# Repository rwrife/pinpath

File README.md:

# PinPath

> USB-powered RP2040 cable and wiring-harness tester for makers to map low-voltage pin continuity, catch opens, shorts, and crossovers, and save local test reports without cloud accounts.

## Overview

PinPath is planned as safe, repairable, open hardware for checking **disconnected, de-energized** passive cables and small wiring harnesses at a desk or workbench. Two configurable 16-position test banks connect through replaceable adapter boards or labeled flying leads. Firmware scans the conductors, reports the observed end-to-end map, and compares it with a user-selected expected map. A local desktop companion creates cable profiles and exports results.

This repository contains the frozen MVP requirements/architecture, a manufacturer-backed **rev-A candidate component selection**, the editable rev-A carrier schematic and routed carrier PCB candidate with source-of-truth BOM and clean native ERC/DRC evidence, RP2040 firmware with host-test scenario coverage, the Tauri 2 companion app with deterministic mock-protocol tests, and assembly/bring-up documentation. It still does not contain a fabricated unit or any bench-test evidence; `hardware/selection/limits-rev-a.json` deliberately keeps scanning unauthorized until physical characterization, and no release tag exists until that evidence does.

## Motivation

Continuity mode on a multimeter works for one conductor at a time, but repetitive multi-pin checks are slow and easy to record incorrectly. Commercial harness testers can be excessive for hobby and repair work. PinPath aims to make common passive-cable checks repeatable while keeping the limits obvious: it is not a live-circuit probe, cable certifier, insulation tester, or safety instrument.

## Target users

- Makers assembling Dupont, JST-style, ribbon, and custom low-voltage harnesses
- Repair hobbyists checking intermittent or miswired passive cables
- Small workshops repeating the same fixture check in low volume
- Electronics learners who want a visible pin-to-pin map

## Concrete use cases

1. Connect both ends of an unpowered 10-conductor ribbon harness through adapters, select its saved profile, and identify one crossed pair.
2. Wiggle a repaired USB-data-only breakout harness during a timed scan and flag intermittent continuity for investigation; do **not** connect a live USB source.
3. Map an undocumented passive cable, label its observed connections, and export JSON/CSV for a project record.
4. Run a fixture self-test using a known loopback adapter before testing a batch.

## Intended workflow

1. Disconnect the cable or harness from every power source and device.
2. Inspect it and connect each end to the appropriate passive adapter or labeled flying leads.
3. Choose **map unknown cable** or an expected cable profile in the desktop app.
4. Start a bounded scan from the app or device button.
5. Review opens, shorts, crossovers, and intermittent observations; save or export the report.
6. Disconnect the item under test before changing adapters.

## MVP features

- Up to 16 conductors per side through two protected test banks
- Deterministic continuity map with open, short, and crossover classification
- Fixture self-test and explicit connected-voltage precheck design requirement
- Physical start/cancel button and non-color-only status indication
- USB CDC protocol; useful offline without Wi-Fi or an account
- Local profile/history storage with versioned JSON backup and CSV report export
- Replaceable adapter interface, starting with pin headers and labeled flying leads

## Non-goals

- Testing energized cables, mains wiring, PoE, batteries or battery packs, powered USB through a test bank, vehicles, medical or life-safety wiring, or unknown live circuits
- USB/Ethernet signal-integrity, bandwidth, impedance, insulation, hipot, precision-resistance, cable certification, or other certification measurements
- Four-wire milliohm measurement or calibrated resistance metrology
- Automatic connector identification
- Cloud dashboards, remote unattended operation, or production-line certification claims

## Safety and electrical limits

PinPath is planned for USB SELV power and de-energized passive assemblies only. The design must detect unexpected external voltage before enabling continuity scans, limit fault current, tolerate routine static handling, and fail visibly. These protections reduce risk but do not make live testing acceptable. Never connect mains, PoE, battery packs, powered USB hosts, vehicles, medical equipment, or safety-critical wiring. Final voltage/current limits will be set only after component datasheet review and measured bring-up.

## Privacy, permissions, and data storage

The desktop app will work locally with no account, telemetry, advertising, or cloud dependency. It requests USB-device access only when the user connects to PinPath and filesystem access only for explicit import/export. Profiles and reports live in an app-local SQLite database. Versioned JSON backup/restore and CSV report export keep the data user-owned. Export can omit free-text project notes.

## Accessibility expectations

All status must be conveyed with text/icon shape in addition to color. The app must support keyboard-only operation, screen readers, scalable text, strong focus indicators, reduced motion, and high-contrast themes. Connector positions and adapter documentation must use durable numbers, not color alone.

## Planned repository layout

```text
hardware/pinpath.kicad_pro    # editable rev-A carrier project
hardware/pinpath.kicad_sch    # editable carrier schematic and BOM source of truth
hardware/pinpath.kicad_pcb    # routed rev-A carrier candidate (see hardware/PCB-layout-evidence.md)
hardware/adapters/            # known-loopback electrical definition; PCB adapters planned
hardware/selection/           # rev-A candidate parts, evidence, calculations, and unvalidated limits
hardware/reports/             # ERC/DRC evidence and host-sim integration matrix
hardware/fab-out/             # gerber/drill/CPL candidates, fab inspection, board renders
firmware/                     # RP2040 safe-state firmware, host tests, scenario matrix, HIL fixture
app/                          # Tauri 2 desktop companion (Rust + TypeScript)
bom/bom.csv                   # schematic-derived tracked BOM
bom/non-schematic-items.csv   # cables, contacts, tools, and mechanical items
docs/                         # architecture, protocol, risk, verification matrix, assembly/bring-up docs
release/                      # release-readiness checklist and checksum generator
```

Final BOM data belongs in **KiCad schematic symbol properties** (including Manufacturer and MPN) and is exported to tracked `bom/bom.csv`. The preliminary CSV remains planning history; neither file is an order or a claim of current stock/price validation.

## Current status and milestones

- **Now:** frozen MVP requirements/architecture, rev-A candidate component selection, editable carrier schematic and routed carrier PCB candidate (0-error DRC, documented residuals), clean native ERC, schematic-derived BOM, RP2040 safe-state firmware with host tests and a 13-scenario integration matrix (host simulation), desktop companion with lint/tests/a11y/build/unsigned-package CI, assembly/bring-up/characterization documentation, and a release-readiness checklist (`release/RELEASE-READINESS.md`). Physical fabrication, assembly, and bench validation remain pending; scanning stays unauthorized until the limits record is validated on real hardware.
- **M1:** requirements, risk analysis, and adapter/test architecture
- **M2:** datasheet-backed component selection, editable KiCad schematic, and clean/documented ERC
- **M3:** PCB, DRC, firmware, protocol, and simulated fixture tests
- **M4:** desktop app, integration bring-up, assembly documentation, and measured limits
- **M5:** inspected fabrication outputs and reproducible release archive

## Development quickstart

The current repeatable static checks are:

```bash
python3 tools/verify_requirements.py
python3 hardware/selection/calculate_frontend.py --output hardware/selection/front-end-analysis.json
python3 -m unittest discover -s hardware/selection -p 'test_*.py' -v
python3 tools/verify_component_selection.py
python3 tools/verify_schematic.py
kicad-cli sch erc hardware/pinpath.kicad_sch --severity-all --exit-code-violations -o hardware/reports/pinpath-erc.rpt
```

After implementation skeletons land, expected commands are:

```bash
# Firmware (planned)
cmake -S firmware -B firmware/build
cmake --build firmware/build
ctest --test-dir firmware/build

# Desktop app (current baseline)
cd app
npm ci
npm run lint
npm run test:ci
npm run a11y
npm run build
npm run tauri:build
```

The firmware commands remain architectural targets. The app commands are now wired in CI and pass locally on this branch. See [PLAN.md](PLAN.md), [system requirements](hardware/requirements.md), [architecture](docs/architecture.md), [risk analysis](docs/risk-analysis.md), [verification matrix](docs/verification-matrix.md), [app/README.md](app/README.md), and [docs/usb-permissions.md](docs/usb-permissions.md) for status and limitations.

## Licensing

Software and documentation are MIT licensed (`LICENSE`); editable KiCad
hardware sources are distributed under the same MIT grant for the rev-A
candidate. Third-party code and documentation references are attributed in
[THIRD_PARTY_NOTICES.md](THIRD_PARTY_NOTICES.md). Manufacturer datasheets cited
in `hardware/selection/evidence-sources.json` remain the property of their
respective manufacturers.

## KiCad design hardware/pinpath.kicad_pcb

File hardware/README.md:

# Hardware plan

## System block description

```text
USB 5 V SELV
    |
[power/protection] -> [RP2040 module + USB CDC]
                            |
                  [protected scan front end]
                     /                \
             [16-pin Bank A]      [16-pin Bank B]
                     |                  |
              passive adapter     passive adapter
                       \              /
                    de-energized cable
```

The rev-A schematic uses Raspberry Pi Pico `SC0915`, eight TI `TMUX1108PWR` muxes for independent stimulus/sense paths, 10 kΩ endpoint current limiting, low-leakage rail clamps, four-channel ESD arrays, and a two-phase 0/1.8 V precheck bias. The editable project is now in `pinpath.kicad_pro` / `pinpath.kicad_sch`; exact references, packages, manufacturer properties, GPIO allocation, and pinout evidence are in [the component-selection handoff](selection/component-selection.md) and [schematic pinout evidence](schematic-pinout-evidence.md). Native KiCad 9 ERC is clean, but this remains static EDA evidence only: `selection/limits-rev-a.json` is still `validated: false`, so no scan is authorized before layout review and bench characterization. Normative behavior and evidence gates remain in [requirements](requirements.md), [architecture](../docs/architecture.md), [risk analysis](../docs/risk-analysis.md), and the [verification matrix](../docs/verification-matrix.md).

## Interfaces

- USB CDC for power, configuration, and reports
- Two keyed 16-position low-voltage test-bank connectors
- Replaceable passive adapters; first targets are numbered headers and labeled flying leads
- SWD or vendor-supported debug connection and a documented recovery path
- Physical start/cancel control and text/shape-capable or coded status indication

## Power plan

USB 5 V SELV enters only through the Pico micro-USB connector; its on-module supply generates 3V3 for the candidate front end. The two-phase precheck requires all 32 endpoints to track both a low bias and the measured 1.8 V reference while every stimulus enable is low. Provisional thresholds and calculated fault currents are recorded in `selection/limits-rev-a.json`, but are explicitly unvalidated and cannot authorize firmware scanning. The design must not source meaningful operating power into the item under test.

## Enclosure and assembly concept

A small screw-fastened or snap-fit printed enclosure will expose the two adapter sockets, USB, button, and status window. The PCB will use hand-assembly-friendly parts where practical, mounting holes, clear pin numbering, probeable test points, and replaceable adapters so connector wear does not require replacing the main board.

## Safety limits

Use only with fully disconnected, de-energized passive cables and harnesses. Never attach mains, PoE, powered USB through a test bank, a battery or battery pack, vehicles, medical or life-safety wiring, or any energized circuit. PinPath makes no cable certification claim and is not a hipot tester, insulation tester, precision ohmmeter, or protective instrument. Protection circuitry cannot make prohibited live testing safe.

## Editable KiCad deliverables

Current schematic-stage sources and evidence are:

- `hardware/pinpath.kicad_pro`
- `hardware/pinpath.kicad_sch`
- `hardware/pinpath.kicad_pcb` (rev-A carrier layout candidate; see [PCB layout evidence](PCB-layout-evidence.md) for DRC status, residuals, and fab-candidate posture)
- `hardware/pinpath.kicad_sym`
- `hardware/pinpath.pretty/RaspberryPi_Pico_SMD_HandSolder.kicad_mod`
- `hardware/TestPoint.pretty/` (project-local micro test points)
- `hardware/schematic-pinout-evidence.md`
- `hardware/PCB-layout-evidence.md`
- `hardware/reports/pinpath-erc.rpt`
- `hardware/reports/drc-20260918-final.json` (0 errors; adjudicated warnings)
- `hardware/reports/pinpath-schematic.pdf` (review supplement, not source)
- `hardware/fab-out/pinpath-gerbers/` + `fab-out/gerber-inspection.json` (inspected release-candidate fabrication outputs)
- `hardware/adapters/known-loopback/` (passive one-to-one electrical fixture definition)
- `bom/bom.csv` (native export from schematic properties)
- `bom/non-schematic-items.csv`

The carrier PCB now exists as a layout candidate with 0-error native DRC;
the single remaining stub, pour-island residual, and adapter cable-assembly
decision are adjudicated in [PCB layout evidence](PCB-layout-evidence.md).
Final Manufacturer/MPN/source data lives in schematic symbol properties and
exports to tracked `bom/bom.csv`; volatile costs remain explicitly `UNKNOWN`
until dated supplier evidence is obtained.

## Issue #7 integration artifacts (2026-09-19)

- `reports/erc-20260919-release.rpt` — native ERC re-run on committed
  schematic: 0 errors / 0 warnings.
- `reports/drc-20260919-release.json` — native DRC re-run including
  schematic-parity: 0 errors, 63 warnings, 66 ratsnest items — identical to
  the 2026-09-18 candidate state; the 4 parity entries are the off-schematic
  mounting holes (intentional, see layout evidence item 4).
- `reports/pinpath-schematic-20260919-release.pdf` — review PDF re-export.
- `reports/integration-scenario-matrix-hostsim.json` — 13-scenario
  integration matrix executed by `firmware/tests/test_scenarios.cpp`;
  `host_simulation` evidence only, not bench evidence.
- `fab-out/renders/` — native `kicad-cli pcb render` top/bottom renders of
  the unpopulated candidate.
- Assembly guide, bring-up checklist, and characterization plan live in
  `../docs/`; the release gate is `../release/RELEASE-READINESS.md`.

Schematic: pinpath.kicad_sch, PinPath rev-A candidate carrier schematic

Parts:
C1, C2, C3, C4, C5, C6, C7, C8, C9: 100nF 16V X7R 10%; C_0805_2012Metric; MPN GRM21BR71C104KA01L
C10: 1uF 16V X7R 10%; C_0805_2012Metric; MPN GRM21BR71C105KA01L
D1, D2, D3, D4, D5, D6, D7, D8, D9, D10, D11, D12, D13, D14, D15, D16, D17, D18, D19, D20, D21, D22, D23, D24, D25, D26, D27, D28, D29, D30, D31, D32: BAS70-04 dual-series clamp; SOT-23; MPN BAS70-04,215
D33, D34, D35, D36, D37, D38, D39, D40: TPD4E1U06 quad ESD; SOT-363_SC-70-6; MPN TPD4E1U06DCKR
D41: READY green; LED_0805_2012Metric; MPN APT2012LZGCK
D42: FAULT red; LED_0805_2012Metric; MPN APTD2012LSURCK
J1: Bank A Micro-Fit 16; Molex_Micro-Fit_3.0_43045-1600_2x08_P3.00mm_Horizontal; MPN 43045-1600
J2: Bank B Micro-Fit 16; Molex_Micro-Fit_3.0_43045-1600_2x08_P3.00mm_Horizontal; MPN 43045-1600
J3: Keyed Cortex 10-pin SWD; PinHeader_2x05_P1.27mm_Vertical_SMD; MPN FTSH-105-01-L-DV-K
R1, R2, R3, R4, R5, R6, R7, R8, R9, R10, R11, R12, R13, R14, R15, R16, R17, R18, R19, R20, R21, R22, R23, R24, R25, R26, R27, R28, R29, R30, R31, R32: 10k 1%; R_0805_2012Metric; MPN CRCW080510K0FKEA
R33, R34, R35, R36, R37, R38, R39, R40, R41, R42, R43, R44, R45, R46, R47, R48, R49, R50, R51, R52, R53, R54, R55, R56, R57, R58, R59, R60, R61, R62, R63, R64, R65, R66, R67, R68, R69, R70, R71, R72, R73, R74, R76: 100k 1%; R_0805_2012Metric; MPN CRCW0805100KFKEA
R75, R77, R78: 1k 1%; R_0805_2012Metric; MPN CRCW08051K00FKEA
SW1: START/CANCEL SPST-NO; SW_Tactile_SPST_NO_Straight_CK_PTS636Sx25SMTRLFS; MPN PTS636SK25FSMTRLFS
TP1: VBUS; TestPoint_Keystone_5015_Micro-Minature; MPN 5015
TP2: +3V3; TestPoint_Keystone_5015_Micro-Minature; MPN 5015
TP3: GND; TestPoint_Keystone_5015_Micro-Minature; MPN 5015
TP4: ADC_REF_1V8; TestPoint_Keystone_5015_Micro-Minature; MPN 5015
TP5: BIAS; TestPoint_Keystone_5015_Micro-Minature; MPN 5015
TP6: STIM; TestPoint_Keystone_5015_Micro-Minature; MPN 5015
TP7: DRV_A_LO_EN; TestPoint_Keystone_5015_Micro-Minature; MPN 5015
TP8: READY_LED; TestPoint_Keystone_5015_Micro-Minature; MPN 5015
TP9: FAULT_LED; TestPoint_Keystone_5015_Micro-Minature; MPN 5015
TP10: A:01_NODE; TestPoint_Keystone_5015_Micro-Minature; MPN 5015
TP11: B:01_NODE; TestPoint_Keystone_5015_Micro-Minature; MPN 5015
TP12: RUN; TestPoint_Keystone_5015_Micro-Minature; MPN 5015
U1: Raspberry Pi Pico SC0915; RaspberryPi_Pico_SMD_HandSolder; MPN SC0915
U2: TMUX1108 U2 DRV_A_LO_EN; TSSOP-16_4.4x5mm_P0.65mm; MPN TMUX1108PWR
U3: TMUX1108 U3 DRV_A_HI_EN; TSSOP-16_4.4x5mm_P0.65mm; MPN TMUX1108PWR
U4: TMUX1108 U4 DRV_B_LO_EN; TSSOP-16_4.4x5mm_P0.65mm; MPN TMUX1108PWR
U5: TMUX1108 U5 DRV_B_HI_EN; TSSOP-16_4.4x5mm_P0.65mm; MPN TMUX1108PWR
U6: TMUX1108 U6 SENSE_LO_EN; TSSOP-16_4.4x5mm_P0.65mm; MPN TMUX1108PWR
U7: TMUX1108 U7 SENSE_HI_EN; TSSOP-16_4.4x5mm_P0.65mm; MPN TMUX1108PWR
U8: TMUX1108 U8 SENSE_LO_EN; TSSOP-16_4.4x5mm_P0.65mm; MPN TMUX1108PWR
U9: TMUX1108 U9 SENSE_HI_EN; TSSOP-16_4.4x5mm_P0.65mm; MPN TMUX1108PWR
U10: REF3318 1.8V; SOT-23; MPN REF3318AIDBZR

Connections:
/+3V3: C1.1, C2.1, C3.1, C4.1, C5.1, C6.1, C7.1, C8.1, C9.1, D1.2 (K2/+3V3), D2.2 (K2/+3V3), D3.2 (K2/+3V3), D4.2 (K2/+3V3), D5.2 (K2/+3V3), D6.2 (K2/+3V3), D7.2 (K2/+3V3), D8.2 (K2/+3V3), D9.2 (K2/+3V3), D10.2 (K2/+3V3), D11.2 (K2/+3V3), D12.2 (K2/+3V3), D13.2 (K2/+3V3), D14.2 (K2/+3V3), D15.2 (K2/+3V3), D16.2 (K2/+3V3), D17.2 (K2/+3V3), D18.2 (K2/+3V3), D19.2 (K2/+3V3), D20.2 (K2/+3V3), D21.2 (K2/+3V3), D22.2 (K2/+3V3), D23.2 (K2/+3V3), D24.2 (K2/+3V3), D25.2 (K2/+3V3), D26.2 (K2/+3V3), D27.2 (K2/+3V3), D28.2 (K2/+3V3), D29.2 (K2/+3V3), D30.2 (K2/+3V3), D31.2 (K2/+3V3), D32.2 (K2/+3V3), J3.1 (VTREF), R76.1, TP2.1, U1.36 (3V3), U2.13 (VDD), U3.13 (VDD), U4.13 (VDD), U5.13 (VDD), U6.13 (VDD), U7.13 (VDD), U8.13 (VDD), U9.13 (VDD), U10.1 (IN)
/A:01: J1.1, R1.1
/A:01_NODE: D1.3 (K1/A2/NODE), D33.1 (D1+), R1.2, R33.1, TP10.1, U2.4 (S1), U6.4 (S1)
/A:02: J1.2, R2.1
/A:02_NODE: D2.3 (K1/A2/NODE), D33.6 (D1-), R2.2, R34.1, U2.5 (S2), U6.5 (S2)
/A:03: J1.3, R3.1
/A:03_NODE: D3.3 (K1/A2/NODE), D33.3 (D2+), R3.2, R35.1, U2.6 (S3), U6.6 (S3)
/A:04: J1.4, R4.1
/A:04_NODE: D4.3 (K1/A2/NODE), D33.4 (D2-), R4.2, R36.1, U2.7 (S4), U6.7 (S4)
/A:05: J1.5, R5.1
/A:05_NODE: D5.3 (K1/A2/NODE), D34.1 (D1+), R5.2, R37.1, U2.12 (S5), U6.12 (S5)
/A:06: J1.6, R6.1
/A:06_NODE: D6.3 (K1/A2/NODE), D34.6 (D1-), R6.2, R38.1, U2.11 (S6), U6.11 (S6)
/A:07: J1.7, R7.1
/A:07_NODE: D7.3 (K1/A2/NODE), D34.3 (D2+), R7.2, R39.1, U2.10 (S7), U6.10 (S7)
/A:08: J1.8, R8.1
/A:08_NODE: D8.3 (K1/A2/NODE), D34.4 (D2-), R8.2, R40.1, U2.9 (S8), U6.9 (S8)
/A:09: J1.9, R9.1
/A:09_NODE: D9.3 (K1/A2/NODE), D35.1 (D1+), R9.2, R41.1, U3.4 (S1), U7.4 (S1)
/A:10: J1.10, R10.1
/A:10_NODE: D10.3 (K1/A2/NODE), D35.6 (D1-), R10.2, R42.1, U3.5 (S2), U7.5 (S2)
/A:11: J1.11, R11.1
/A:11_NODE: D11.3 (K1/A2/NODE), D35.3 (D2+), R11.2, R43.1, U3.6 (S3), U7.6 (S3)
/A:12: J1.12, R12.1
/A:12_NODE: D12.3 (K1/A2/NODE), D35.4 (D2-), R12.2, R44.1, U3.7 (S4), U7.7 (S4)
/A:13: J1.13, R13.1
/A:13_NODE: D13.3 (K1/A2/NODE), D36.1 (D1+), R13.2, R45.1, U3.12 (S5), U7.12 (S5)
/A:14: J1.14, R14.1
/A:14_NODE: D14.3 (K1/A2/NODE), D36.6 (D1-), R14.2, R46.1, U3.11 (S6), U7.11 (S6)
/A:15: J1.15, R15.1
/A:15_NODE: D15.3 (K1/A2/NODE), D36.3 (D2+), R15.2, R47.1, U3.10 (S7), U7.10 (S7)
/A:16: J1.16, R16.1
/A:16_NODE: D16.3 (K1/A2/NODE), D36.4 (D2-), R16.2, R48.1, U3.9 (S8), U7.9 (S8)
/ADC_REF_1V8: C10.1, R75.1, TP4.1, U1.34 (GP28_ADC2), U10.2 (OUT)
/B:01: J2.1, R17.1
/B:01_NODE: D17.3 (K1/A2/NODE), D37.1 (D1+), R17.2, R49.1, TP11.1, U4.4 (S1), U8.4 (S1)
/B:02: J2.2, R18.1
/B:02_NODE: D18.3 (K1/A2/NODE), D37.6 (D1-), R18.2, R50.1, U4.5 (S2), U8.5 (S2)
/B:03: J2.3, R19.1
/B:03_NODE: D19.3 (K1/A2/NODE), D37.3 (D2+), R19.2, R51.1, U4.6 (S3), U8.6 (S3)
/B:04: J2.4, R20.1
/B:04_NODE: D20.3 (K1/A2/NODE), D37.4 (D2-), R20.2, R52.1, U4.7 (S4), U8.7 (S4)
/B:05: J2.5, R21.1
/B:05_NODE: D21.3 (K1/A2/NODE), D38.1 (D1+), R21.2, R53.1, U4.12 (S5), U8.12 (S5)
/B:06: J2.6, R22.1
/B:06_NODE: D22.3 (K1/A2/NODE), D38.6 (D1-), R22.2, R54.1, U4.11 (S6), U8.11 (S6)
/B:07: J2.7, R23.1
/B:07_NODE: D23.3 (K1/A2/NODE), D38.3 (D2+), R23.2, R55.1, U4.10 (S7), U8.10 (S7)
/B:08: J2.8, R24.1
/B:08_NODE: D24.3 (K1/A2/NODE), D38.4 (D2-), R24.2, R56.1, U4.9 (S8), U8.9 (S8)
/B:09: J2.9, R25.1
/B:09_NODE: D25.3 (K1/A2/NODE), D39.1 (D1+), R25.2, R57.1, U5.4 (S1), U9.4 (S1)
/B:10: J2.10, R26.1
/B:10_NODE: D26.3 (K1/A2/NODE), D39.6 (D1-), R26.2, R58.1, U5.5 (S2), U9.5 (S2)
/B:11: J2.11, R27.1
/B:11_NODE: D27.3 (K1/A2/NODE), D39.3 (D2+), R27.2, R59.1, U5.6 (S3), U9.6 (S3)
/B:12: J2.12, R28.1
/B:12_NODE: D28.3 (K1/A2/NODE), D39.4 (D2-), R28.2, R60.1, U5.7 (S4), U9.7 (S4)
/B:13: J2.13, R29.1
/B:13_NODE: D29.3 (K1/A2/NODE), D40.1 (D1+), R29.2, R61.1, U5.12 (S5), U9.12 (S5)
/B:14: J2.14, R30.1
/B:14_NODE: D30.3 (K1/A2/NODE), D40.6 (D1-), R30.2, R62.1, U5.11 (S6), U9.11 (S6)
/B:15: J2.15, R31.1
/B:15_NODE: D31.3 (K1/A2/NODE), D40.3 (D2+), R31.2, R63.1, U5.10 (S7), U9.10 (S7)
/B:16: J2.16, R32.1
/B:16_NODE: D32.3 (K1/A2/NODE), D40.4 (D2-), R32.2, R64.1, U5.9 (S8), U9.9 (S8)
/BIAS: R33.2, R34.2, R35.2, R36.2, R37.2, R38.2, R39.2, R40.2, R41.2, R42.2, R43.2, R44.2, R45.2, R46.2, R47.2, R48.2, R49.2, R50.2, R51.2, R52.2, R53.2, R54.2, R55.2, R56.2, R57.2, R58.2, R59.2, R60.2, R61.2, R62.2, R63.2, R64.2, R75.2, TP5.1, U1.14 (GP10)
/DRV_A_HI_EN: R66.1, U1.6 (GP4), U3.2 (EN)
/DRV_A_LO_EN: R65.1, TP7.1, U1.5 (GP3), U2.2 (EN)
/DRV_B_HI_EN: R68.1, U1.9 (GP6), U5.2 (EN)
/DRV_B_LO_EN: R67.1, U1.7 (GP5), U4.2 (EN)
/FAULT_LED: R78.1, TP9.1, U1.17 (GP13)
/FAULT_LED_A: D42.2 (A), R78.2
/GND: C1.2, C2.2, C3.2, C4.2, C5.2, C6.2, C7.2, C8.2, C9.2, C10.2, D1.1 (A1/GND), D2.1 (A1/GND), D3.1 (A1/GND), D4.1 (A1/GND), D5.1 (A1/GND), D6.1 (A1/GND), D7.1 (A1/GND), D8.1 (A1/GND), D9.1 (A1/GND), D10.1 (A1/GND), D11.1 (A1/GND), D12.1 (A1/GND), D13.1 (A1/GND), D14.1 (A1/GND), D15.1 (A1/GND), D16.1 (A1/GND), D17.1 (A1/GND), D18.1 (A1/GND), D19.1 (A1/GND), D20.1 (A1/GND), D21.1 (A1/GND), D22.1 (A1/GND), D23.1 (A1/GND), D24.1 (A1/GND), D25.1 (A1/GND), D26.1 (A1/GND), D27.1 (A1/GND), D28.1 (A1/GND), D29.1 (A1/GND), D30.1 (A1/GND), D31.1 (A1/GND), D32.1 (A1/GND), D33.2 (GND), D34.2 (GND), D35.2 (GND), D36.2 (GND), D37.2 (GND), D38.2 (GND), D39.2 (GND), D40.2 (GND), D41.1 (K), D42.1 (K), J3.3 (GND), J3.5 (GND), J3.9 (GND_DETECT), R65.2, R66.2, R67.2, R68.2, R69.2, R70.2, R71.2, R72.2, R73.2, R74.2, SW1.2, TP3.1, U1.3 (GND), U1.8 (GND), U1.13 (GND), U1.18 (GND), U1.23 (GND), U1.28 (GND), U1.33 (AGND), U1.38 (GND), U1.D2 (SWD_GND), U2.3 (VSS), U2.14 (GND), U3.3 (VSS), U3.14 (GND), U4.3 (VSS), U4.14 (GND), U5.3 (VSS), U5.14 (GND), U6.3 (VSS), U6.14 (GND), U7.3 (VSS), U7.14 (GND), U8.3 (VSS), U8.14 (GND), U9.3 (VSS), U9.14 (GND), U10.3 (GND)
/MUX_A0: R71.1, U1.1 (GP0), U2.1 (A0), U3.1 (A0), U4.1 (A0), U5.1 (A0), U6.1 (A0), U7.1 (A0), U8.1 (A0), U9.1 (A0)
/MUX_A1: R72.1, U1.2 (GP1), U2.16 (A1), U3.16 (A1), U4.16 (A1), U5.16 (A1), U6.16 (A1), U7.16 (A1), U8.16 (A1), U9.16 (A1)
/MUX_A2: R73.1, U1.4 (GP2), U2.15 (A2), U3.15 (A2), U4.15 (A2), U5.15 (A2), U6.15 (A2), U7.15 (A2), U8.15 (A2), U9.15 (A2)
/READY_LED: R77.1, TP8.1, U1.16 (GP12)
/READY_LED_A: D41.2 (A), R77.2
/RUN: J3.10 (nRESET), TP12.1, U1.30 (RUN)
/SENSE_A: U1.31 (GP26_ADC0), U6.8 (D), U7.8 (D)
/SENSE_B: U1.32 (GP27_ADC1), U8.8 (D), U9.8 (D)
/SENSE_HI_EN: R70.1, U1.11 (GP8), U7.2 (EN), U9.2 (EN)
/SENSE_LO_EN: R69.1, U1.10 (GP7), U6.2 (EN), U8.2 (EN)
/START_CANCEL_N: R76.2, SW1.1, U1.15 (GP11)
/STIM: R74.1, TP6.1, U1.12 (GP9), U2.8 (D), U3.8 (D), U4.8 (D), U5.8 (D)
/SWCLK: J3.4 (SWCLK/TCK), U1.D1 (SWCLK)
/SWDIO: J3.2 (SWDIO/TMS), U1.D3 (SWDIO)
/VBUS: TP1.1, U1.40 (VBUS)

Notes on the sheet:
PINPATH — DISCONNECTED, DE-ENERGIZED PASSIVE ASSEMBLIES ONLY
Never connect mains, PoE, batteries/battery packs, powered USB through a test bank, vehicles, medical/life-safety wiring, or any energized circuit.
Protection and precheck reduce ordinary fault stress; they do not authorize live testing or create cable-certification, hipot, insulation, or precision-resistance capability.
USB / controller / controls / debug
Stimulus and sense muxes — active-high enables have external 100k pulldowns
Bank A protected endpoint networks
Bank B protected endpoint networks
All electrical limits remain unvalidated; firmware_scan_authorized=false until controlled bench characterization.
READY ✓ (green is supplemental)
FAULT ! (red is supplemental; distinct cue)

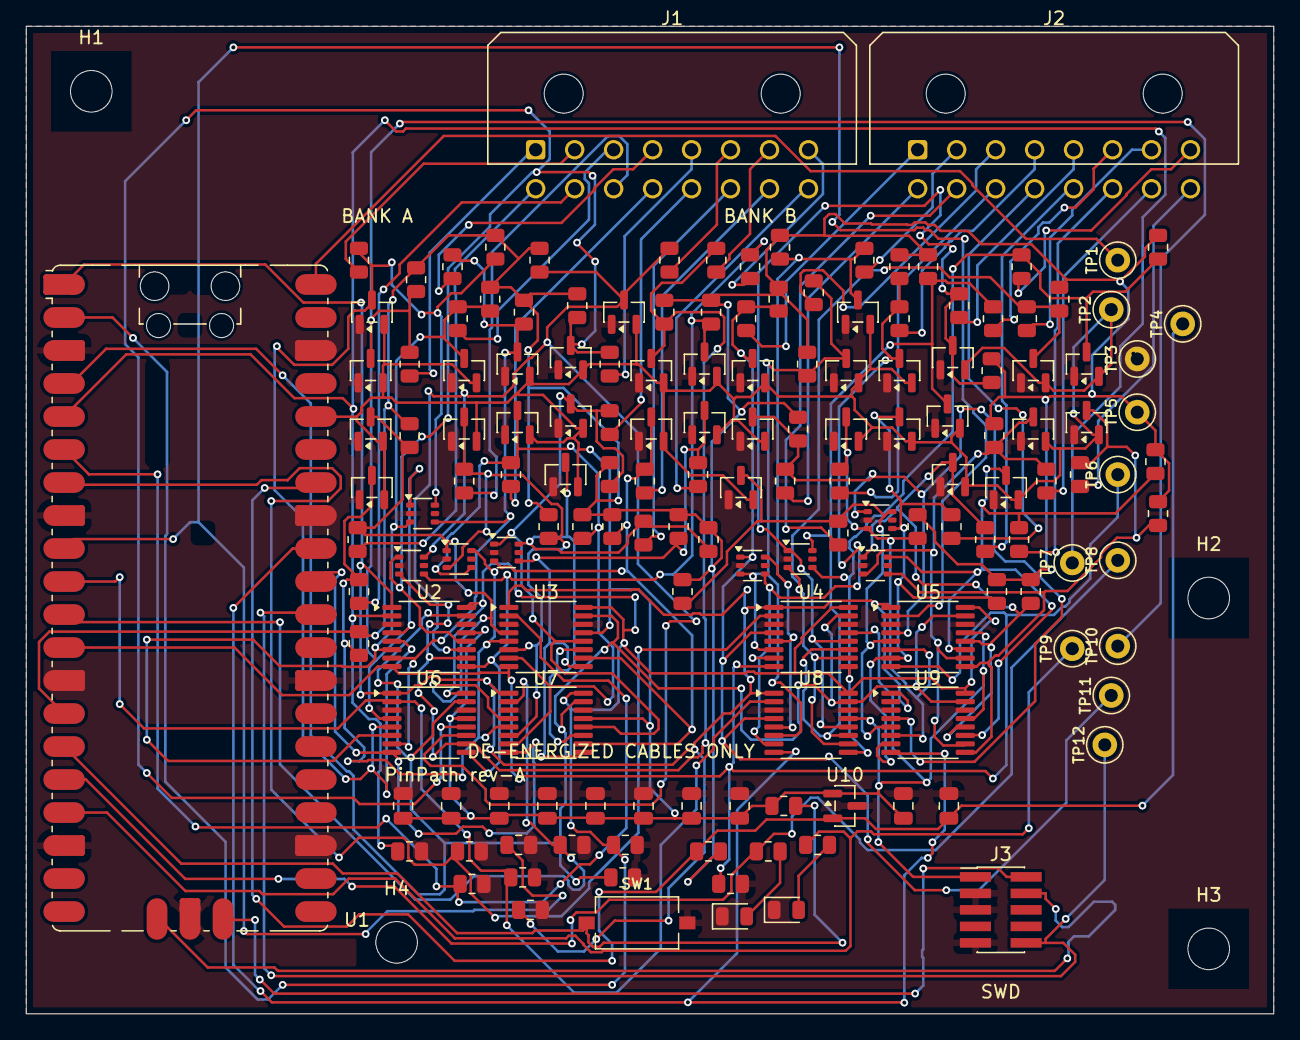
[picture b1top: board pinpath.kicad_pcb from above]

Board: 2 copper layers, 96.0 x 76.0 mm, 160 parts (0 on the bottom side), 89 nets.

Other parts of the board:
H1, H2, H3, H4: MountingHole_3.2mm_M3

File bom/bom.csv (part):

"References","Quantity","Value or Description","Footprint or Package","Manufacturer","MPN","Supplier","Source URL","Estimated Unit Cost USD","Datasheet","Notes","Evidence Status"
"C1-C9","9","100nF 16V X7R 10%","Capacitor_SMD:C_0805_2012Metric","Murata Manufacturing Co., Ltd.","GRM21BR71C104KA01L","authorized distributor TBD before order","https://pim.murata.com/en-global/pim/details/?partNum=GRM21B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","UNKNOWN","https://pim.murata.com/en-global/pim/details/?partNum=GRM21B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","C1-C8 at U2-U9 VDD pins; C9 at REF3318 input. Place directly at supply pins.","manufacturer-datasheet-backed static selection; not bench validated"
"C10","1","1uF 16V X7R 10%","Capacitor_SMD:C_0805_2012Metric","Murata Manufacturing Co., Ltd.","GRM21BR71C105KA01L","authorized distributor TBD before order","https://pim.murata.com/en-global/pim/details/?partNum=GRM21B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","UNKNOWN","https://pim.murata.com/en-global/pim/details/?partNum=GRM21B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","REF3318 output/bias reservoir. Confirm latest TI stability guidance during schematic review.","manufacturer-datasheet-backed static selection; not bench validated"
"D1-D32","32","BAS70-04 dual-series clamp","Package_TO_SOT_SMD:SOT-23","Nexperia B.V.","BAS70-04,215","manufacturer/direct or authorized distributor","https://www.nexperia.com/product/BAS70-04","UNKNOWN","https://assets.nexperia.com/documents/data-sheet/BAS70-04.pdf","Pin 3 is the protected node, pin 1 GND, pin 2 +3V3. Verify this dual-series pin map; do not substitute common-anode/common-cathode variants.","manufacturer-datasheet-backed static selection; not bench validated"
"D33-D40","8","TPD4E1U06 quad ESD","Package_TO_SOT_SMD:SOT-363_SC-70-6","Texas Instruments","TPD4E1U06DCKR","DigiKey","https://www.digikey.com/en/products/detail/texas-instruments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","UNKNOWN","https://www.ti.com/lit/ds/symlink/tpd4e1u06.pdf","One device per four protected internal endpoint nodes, after the 10 kOhm connector series resistors. Place with a short direct ground return. ESD treatment does not authorize energized testing.","manufacturer-datasheet-backed static selection; not bench validated"
"D41","1","READY green","LED_SMD:LED_0805_2012Metric","Kingbright Electronic Co., Ltd.","APT2012LZGCK","DigiKey","https://www.digikey.com/en/products/detail/kingbright/APT201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","UNKNOWN","https://www.kingbrightusa.com/images/catalog/spec/APT2012LZGCK.pdf","Silkscreen text READY and a distinct ready icon are required; color alone is not status. Verify cathode marking.","manufacturer-datasheet-backed static selection; not bench validated"
"D42","1","FAULT red","LED_SMD:LED_0805_2012Metric","Kingbright Electronic Co., Ltd.","APTD2012LSURCK","DigiKey","https://www.digikey.com/en/products/detail/kingbright/APTD20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","UNKNOWN","https://www.kingbrightusa.com/images/catalog/spec/APTD2012LS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","Silkscreen text FAULT and a distinct fault icon are required; do not reuse READY's non-color cue. Verify cathode marking.","manufacturer-datasheet-backed static selection; not bench validated"
"J1","1","Bank A Micro-Fit 16","Connector_Molex:Molex_Micro-Fit_3.0_43045-1600_2x08_P3.00mm_Horizontal","Molex, LLC","43045-1600","authorized distributor TBD before order","https://www.molex.com/en-us/products/part-detail/430451600","UNKNOWN","https://www.molex.com/en-us/products/part-detail/430451600","J1 Bank A and J2 Bank B. Silkscreen must show bank, A:01-A:16/B:01-B:16 sequence, mating-face drawing direction, key, and pin 1. Verify connector drawing pad numbering in issue #3.","manufacturer-datasheet-backed static selection; not bench validated"
"J2","1","Bank B Micro-Fit 16","Connector_Molex:Molex_Micro-Fit_3.0_43045-1600_2x08_P3.00mm_Horizontal","Molex, LLC","43045-1600","authorized distributor TBD before order","https://www.molex.com/en-us/products/part-detail/430451600","UNKNOWN","https://www.molex.com/en-us/products/part-detail/430451600","J1 Bank A and J2 Bank B. Silkscreen must show bank, A:01-A:16/B:01-B:16 sequence, mating-face drawing direction, key, and pin 1. Verify connector drawing pad numbering in issue #3.","manufacturer-datasheet-backed static selection; not bench validated"
"J3","1","Keyed Cortex 10-pin SWD","Connector_PinHeader_1.27mm:PinHeader_2x05_P1.27mm_Vertical_SMD","Samtec, Inc.","FTSH-105-01-L-DV-K","DigiKey","https://www.digikey.com/en/products/detail/samtec-inc/FTSH-1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","UNKNOWN","https://www.samtec.com/products/ftsh-105-01-l-dv-k","Controller-only SWD/recovery. VTREF is sense-only from 3V3; do not accept debugger power and do not expose any test-bank power path.","manufacturer-datasheet-backed static selection; not bench validated"
"R1-R32","32","10k 1%","Resistor_SMD:R_0805_2012Metric","Vishay Dale","CRCW080510K0FKEA","DigiKey","https://www.digikey.com/en/products/detail/vishay-dale/CRCW0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","UNKNOWN","https://www.vishay.com/docs/20035/dcrcwe3.pdf","Exactly one resistor at each connector entry before the protected internal node. Do not bypass on adapters. Standard-mode ratings used: 0.125 W and 150 V.","manufacturer-datasheet-backed static selection; not bench validated"
"R33-R74,R76","43","100k 1%","Resistor_SMD:R_0805_2012Metric","Vishay Dale","CRCW0805100KFKEA","authorized distributor TBD before order","https://www.vishay.com/docs/20035/dcrcwe3.pdf","UNKNOWN","https://www.vishay.com/docs/20035/dcrcwe3.pdf","R33-R64 endpoint node to BIAS; R65-R70 six enable-net pulldowns; R71-R73 address pulldowns; R74 STIM pulldown; R76 START_CANCEL_N pullup. Preserve active-drive EN defaults low.","manufacturer-datasheet-backed static selection; not bench validated"
"R75,R77,R78","3","1k 1%","Resistor_SMD:R_0805_2012Metric","Vishay Dale","CRCW08051K00FKEA","DigiKey","https://www.digikey.com/en/products/detail/vishay-dale/CRCW0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","UNKNOWN","https://www.vishay.com/docs/20035/dcrcwe3.pdf","R75 feeds REF3318 output to BIAS; BIAS_CTRL may pull low or be high-Z only. R77/R78 limit READY/FAULT LED current.","manufacturer-datasheet-backed static selection; not bench validated"
"SW1","1","START/CANCEL SPST-NO","Button_Switch_SMD:SW_Tactile_SPST_NO_Straight_CK_PTS636Sx25SMTRLFS","C&K (Littelfuse)","PTS636SK25FSMTRLFS","DigiKey","https://www.digikey.com/en/products/detail/c-k/PTS636SK25FSM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","UNKNOWN","https://www.ckswitches.com/media/2779/pts636.pdf","Single deliberate local control; label START/CANCEL. Latest PDF requires manual retrieval because automated download returned HTTP 403.","manufacturer-datasheet-backed static selection; not bench validated"
"TP1","1","VBUS","TestPoint:TestPoint_Keystone_5015_Micro-Minature","Keystone Electronics Corp.","5015","DigiKey","https://www.digikey.com/en/products/detail/keystone-electron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","UNKNOWN","https://www.keyelco.com/pdfs/p33.pdf","Reserve named points for VBUS, 3V3, GND, ADC_REF_1V8, BIAS, STIM, a drive-enable control, READY, FAULT, A:01 internal, B:01 internal, and RUN/reset. Issue #3 may add points but must not remove required coverage.","manufacturer-datasheet-backed static selection; not bench validated"
"TP2","1","+3V3","TestPoint:TestPoint_Keystone_5015_Micro-Minature","Keystone Electronics Corp.","5015","DigiKey","https://www.digikey.com/en/products/detail/keystone-electron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","UNKNOWN","https://www.keyelco.com/pdfs/p33.pdf","Reserve named points for VBUS, 3V3, GND, ADC_REF_1V8, BIAS, STIM, a drive-enable control, READY, FAULT, A:01 internal, B:01 internal, and RUN/reset. Issue #3 may add points but must not remove required coverage.","manufacturer-datasheet-backed static selection; not bench validated"
"TP3","1","GND","TestPoint:TestPoint_Keystone_5015_Micro-Minature","Keystone Electronics Corp.","5015","DigiKey","https://www.digikey.com/en/products/detail/keystone-electron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","UNKNOWN","https://www.keyelco.com/pdfs/p33.pdf","Reserve named points for VBUS, 3V3, GND, ADC_REF_1V8, BIAS, STIM, a drive-enable control, READY, FAULT, A:01 internal, B:01 internal, and RUN/reset. Issue #3 may add points but must not remove required coverage.","manufacturer-datasheet-backed static selection; not bench validated"
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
